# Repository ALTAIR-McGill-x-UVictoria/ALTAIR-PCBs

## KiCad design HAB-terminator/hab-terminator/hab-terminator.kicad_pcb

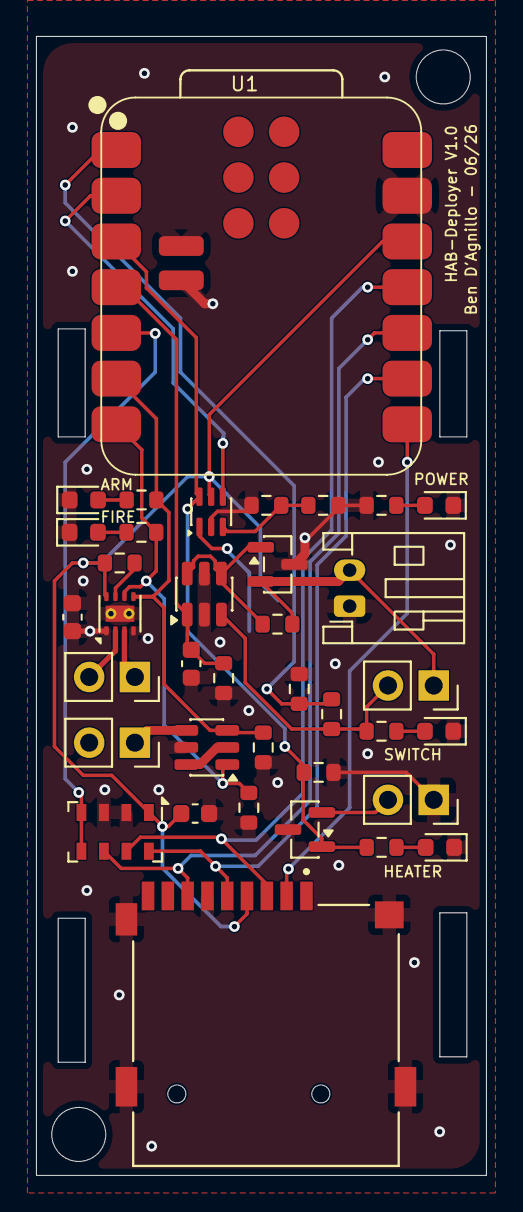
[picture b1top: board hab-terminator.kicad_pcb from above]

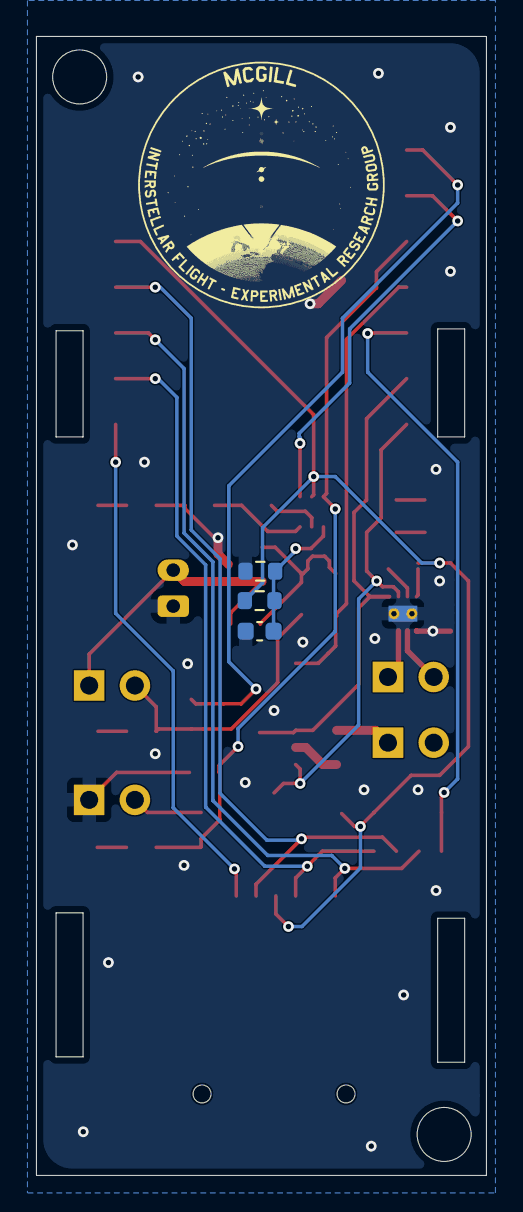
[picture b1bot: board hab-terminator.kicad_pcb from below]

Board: 4 copper layers, 25.0 x 63.3 mm, 40 parts (3 on the bottom side), 29 nets.

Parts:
C2, C4, C6, C7: 100nF; C_0603_1608Metric
D1, D2, D3, D4, D5: LED; LED_0603_1608Metric
J1: Battery; JST_PH_S2B-PH-K_1x02_P2.00mm_Horizontal
J2: Burn wire; PinSocket_1x02_P2.54mm_Vertical
J3: Actuator; PinSocket_1x02_P2.54mm_Vertical
J4: MSD-4-A; CUI_MSD-4-A
J5: Heater; PinSocket_1x02_P2.54mm_Vertical
Q1, Q2: DMN2053UVTQ-7; TSOT-23-6
Q3, Q4: AO3401A; SOT-23
R3, R4, R5, R16, R19: 330; R_0603_1608Metric
R8, R11, R13, R14, R17, R18, R20, R21: 100k; R_0603_1608Metric
R9, R10, R12: 10k; R_0603_1608Metric
SW2: SW_Push_EXT; PinSocket_1x02_P2.54mm_Vertical
TH1: NCU18XH103F60RB; R_0603_1608Metric
U1: XIAO-ESP32-C3-SMD
U2: DRV8212P; WSON-8-1EP_2x2mm_P0.5mm_EP0.9x1.6mm_ThermalVias
U3: 74LVC1G3157; SOT-363_SC-70-6
U4: MS5607-02BA; LGA-8_3x5mm_P1.25mm

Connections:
+3V3: C6.1, J4.4 (VDD), R9.2, R10.2, U1.12 (3V3), U2.8 (VCC), U3.5 (VCC), U4.1 (VDD)
/BURN_ARM/ACT_2: Q1.3 (G), R4.2, R14.1, U1.6 (GPIO7_D5_SCL), U2.5 (IN2)
/BURN_EN/ACT_1: Q1.1 (G), R3.2, R8.1, U1.7 (GPIO21_D6_TX), U2.6 (IN1)
/HEATER_EN/A_MUX: Q4.1 (G), R5.2, R17.2, U1.3 (GPIO4_A2_D2), U3.6
/MS5607_CS: U1.5 (GPIO6_D4_SDA), U4.4 (CSB), U4.5 (CSB)
/NTC: C2.1, R9.1, TH1.1, U3.1
/NTC/VBAT_SNS: U1.2 (GPIO3_A1_D1), U3.4
/PWR_HOLD: C7.2, Q2.1 (G), R12.2, U1.4 (GPIO5_A3_D3)
/SD_CS: J4.2 (CD/DAT3), U1.8 (GPIO20_D7_RX)
/SPI_CLK: J4.5 (CLK), U1.9 (GPIO8_D8_SCK), U4.8 (SCLK)
/SPI_MISO: J4.7 (DAT0), U1.10 (GPIO9_D9_MISO), U4.6 (SDO)
/SPI_MOSI: J4.3 (CMD), U1.11 (GPIO10_D10_MOSI), U4.7 (SDI/SDA)
/SW_SNS: R11.1, R18.2, U1.1 (GPIO2_A0_D0)
/VBAT: J1.2, Q3.2 (S), R13.1, SW2.1
GND: C2.2, C4.1, C4.2, C6.2, C7.1, D1.1 (K), D2.1 (K), D3.1 (K), D4.1 (K), D5.1 (K), J1.1, J4.6 (VSS), J4.G1 (COVER_GND), J4.G2 (COVER_GND__1), J4.G3 (COVER_GND__2), J4.G4 (COVER_GND__3), J5.1, Q1.5 (S), Q2.2 (S), Q2.5 (S), Q3.3 (D), Q4.3 (D), R8.2, R12.1, R14.2, R17.1, R18.1, R19.2, R20.1, R21.1, TH1.2, U1.13 (GND), U1.21 (BAT), U1.22 (GND), U2.1 (VM), U2.4 (GND), U2.9 (GND), U3.2 (GND), U4.2 (PS), U4.3 (GND)
unnamed: D1.2 (A), R3.1
unnamed: D2.2 (A), R4.1
unnamed: D3.2 (A), R16.1
unnamed: D4.2 (A), R19.1
unnamed: D5.2 (A), R5.1
unnamed: J2.1, Q1.4 (D)
unnamed: J3.1, U2.3 (OUT2)
unnamed: J3.2, U2.2 (OUT1)
unnamed: J5.2, Q4.2 (S)
unnamed: Q1.2 (S), Q1.6 (D)
unnamed: Q2.4 (D), Q2.6 (D), Q3.1 (G), R13.2
unnamed: Q2.3 (G), R11.2, R16.2, SW2.2
unnamed: R20.2, R21.2, U3.3
unnamed: R10.1, U2.7 (~SLEEP)

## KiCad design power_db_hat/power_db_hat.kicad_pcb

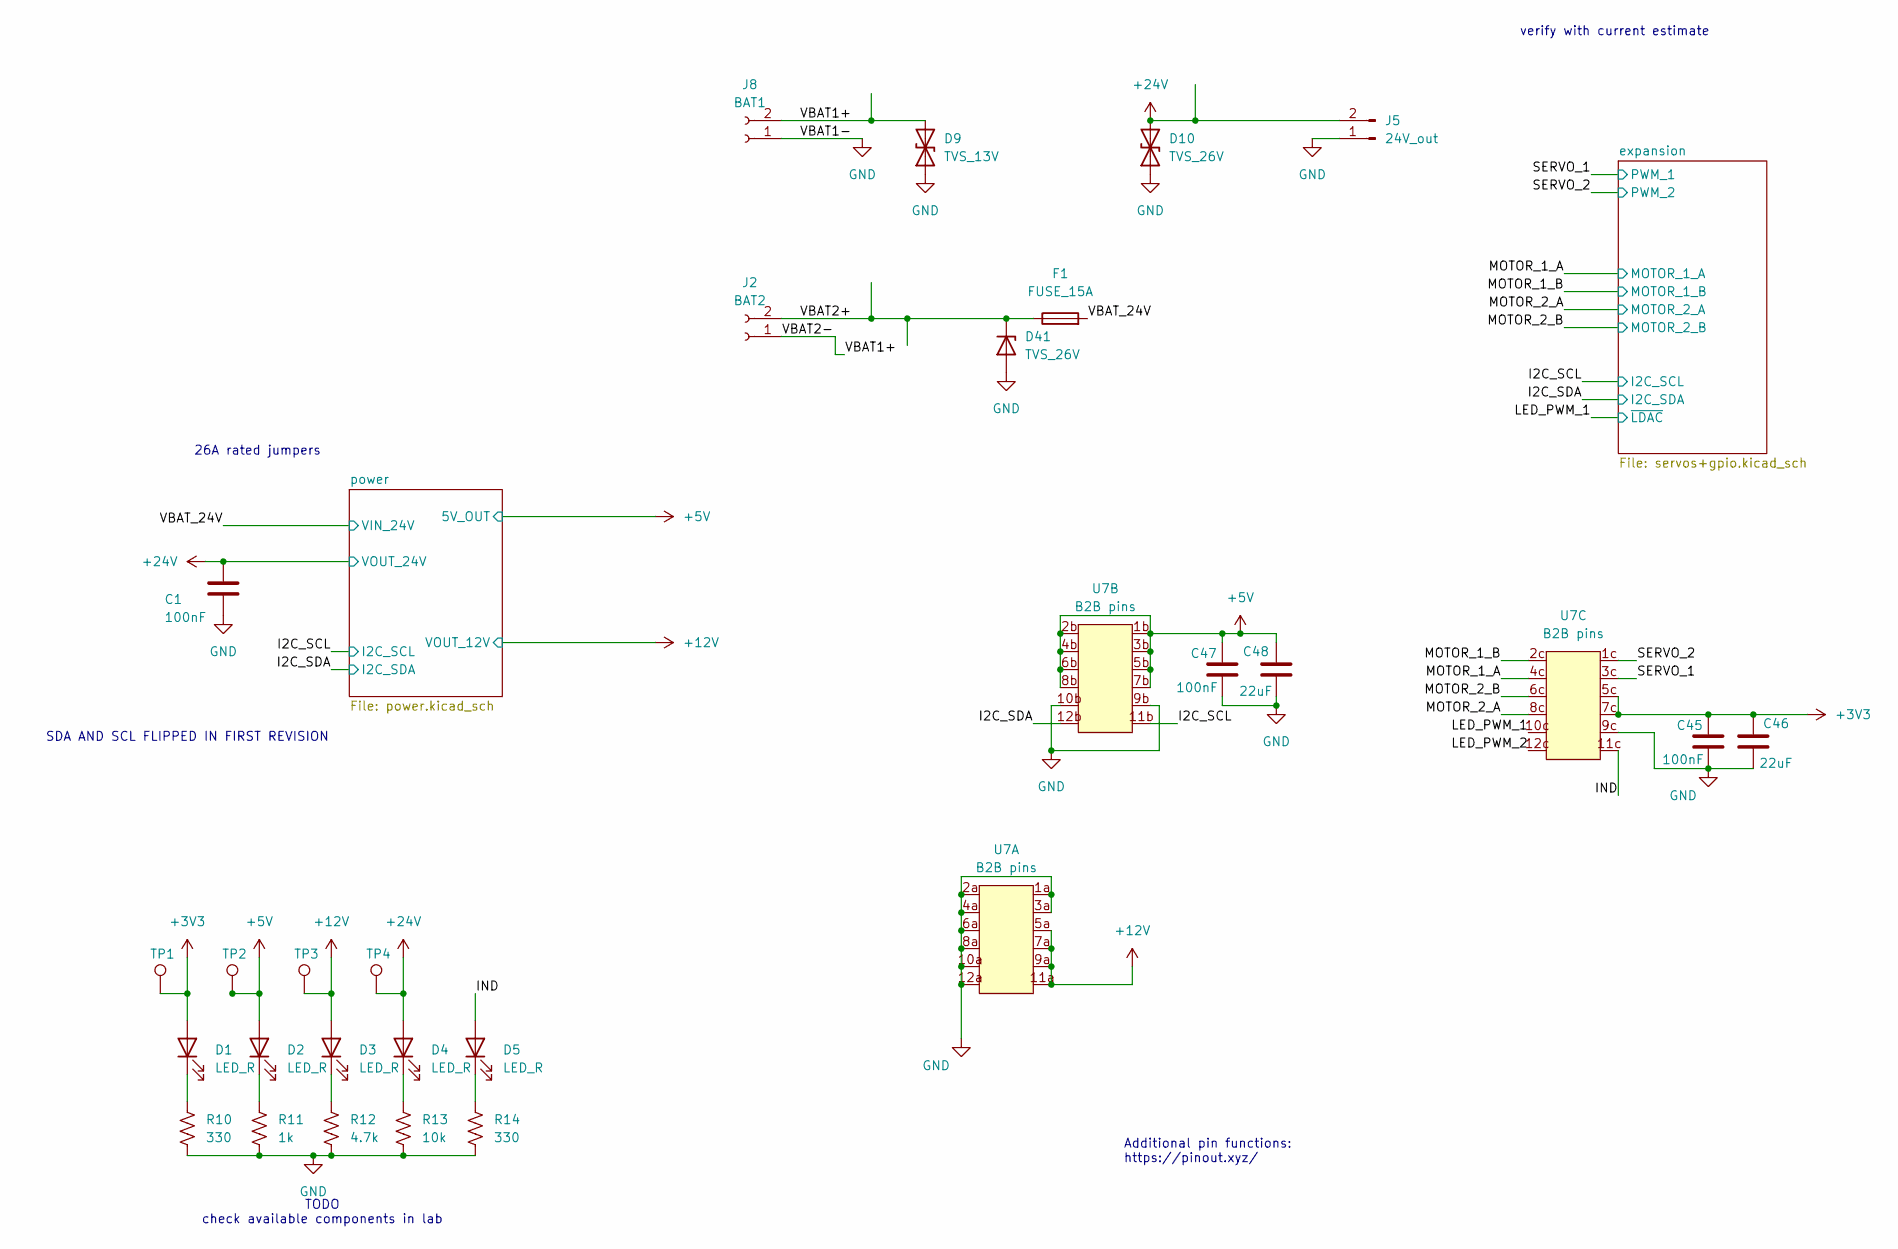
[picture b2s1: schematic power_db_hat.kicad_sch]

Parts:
C1, C45, C47: 100nF; C_0603_1608Metric_Pad1.08x0.95mm_HandSolder
C46, C48: 22uF; C_0805_2012Metric
D1, D2, D3, D4, D5: LED_R; LED_0603_1608Metric_Pad1.05x0.95mm_HandSolder
D9: TVS_13V; D_SMA_Handsoldering
D10, D41: TVS_26V; D_SMA_Handsoldering
F1: FUSE_15A; Fuse_1206_3216Metric_Pad1.42x1.75mm_HandSolder
J2: BAT2; AMASS_XT60PW-M_1x02_P7.20mm_Horizontal
J5: 24V_out; AMASS_XT60PW-F_1x02_P7.20mm_Horizontal
J8: BAT1; AMASS_XT60PW-M_1x02_P7.20mm_Horizontal
R10, R14: 330; R_0603_1608Metric_Pad0.98x0.95mm_HandSolder
R11: 1k; R_0603_1608Metric_Pad0.98x0.95mm_HandSolder
R12: 4.7k; R_0603_1608Metric_Pad0.98x0.95mm_HandSolder
R13: 10k; R_0603_1608Metric_Pad0.98x0.95mm_HandSolder
TP1, TP2, TP3, TP4: TestPoint; TestPoint_Pad_D1.0mm
U7: B2B pins; B2B_pin_socket_3x(02x06)

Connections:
+3V3: C45.2, C46.1, D1.2 (A), TP1.1 (1_1), U7.5c, U7.7c; also elsewhere on the board
+5V: C47.2, C48.1, D2.2 (A), TP2.1 (1_1), U7.1b, U7.2b, U7.3b, U7.4b, U7.5b, U7.6b, U7.7b, U7.8b; also elsewhere on the board
+12V: D3.2 (A), TP3.1 (1_1), U7.5a, U7.7a, U7.9a, U7.11a; also elsewhere on the board
+24V: C1.2, D4.2 (A), D10.2 (A2), J5.2, TP4.1 (1_1); also elsewhere on the board
/I2C_SCL: U7.11b; also elsewhere on the board
/I2C_SDA: U7.12b; also elsewhere on the board
/IND: D5.2 (A), U7.11c
/LED_PWM_1: U7.10c; also elsewhere on the board
/LED_PWM_2: U7.12c
/MOTOR_1_A: U7.4c; also elsewhere on the board
/MOTOR_1_B: U7.2c; also elsewhere on the board
/MOTOR_2_A: U7.8c; also elsewhere on the board
/MOTOR_2_B: U7.6c; also elsewhere on the board
/SERVO_1: U7.3c; also elsewhere on the board
/SERVO_2: U7.1c; also elsewhere on the board
/VBAT1+: D9.2 (A2), J2.1, J8.2
/VBAT2+: D41.1 (K), F1.1, J2.2
/VBAT_24V: F1.2; also elsewhere on the board
GND: C1.1, C45.1, C46.2, C47.1, C48.2, D9.1 (A1), D10.1 (A1), D41.2 (A), J5.1, J8.1, R10.2, R11.2, R12.2, R13.2, R14.2, U7.1a, U7.2a, U7.3a, U7.4a, U7.6a, U7.8a, U7.9b, U7.9c, U7.10a, U7.10b, U7.12a; also elsewhere on the board
unnamed: D1.1 (K), R10.1
unnamed: D2.1 (K), R11.1
unnamed: D3.1 (K), R12.1
unnamed: D4.1 (K), R13.1
unnamed: D5.1 (K), R14.1

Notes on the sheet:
SDA AND SCL FLIPPED IN FIRST REVISION
TODO check available components in lab
Additional pin functions: https://pinout.xyz/
verify with current estimate
26A rated jumpers

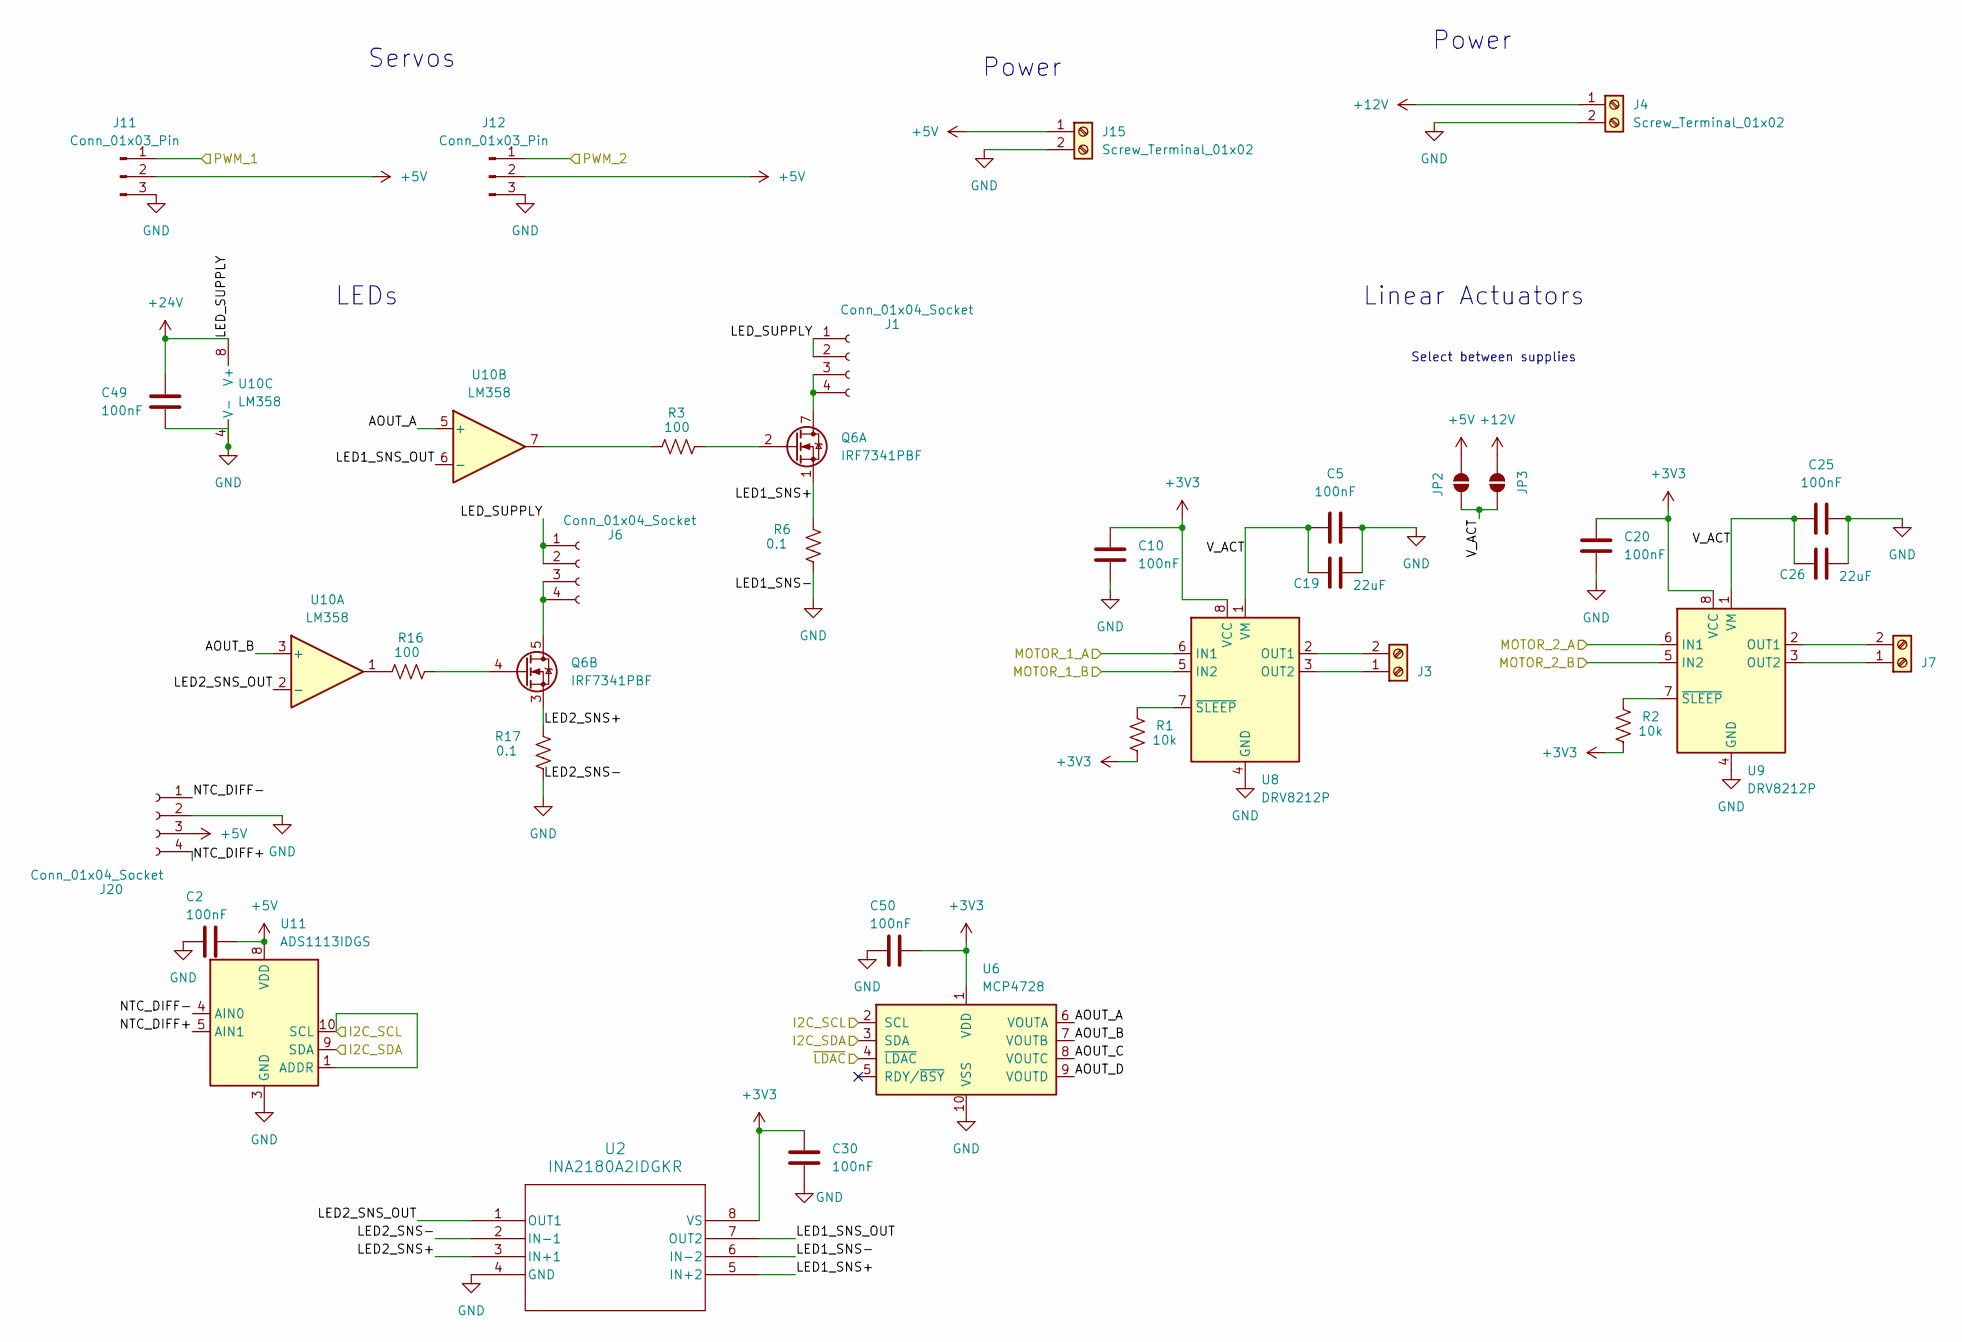
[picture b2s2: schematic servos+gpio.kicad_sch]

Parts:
C2, C5, C10, C20, C25, C30, C49, C50: 100nF; C_0603_1608Metric_Pad1.08x0.95mm_HandSolder
C19, C26: 22uF; C_0805_2012Metric
J1, J6, J20: Conn_01x04_Socket; JST_GH_SM04B-GHS-TB_1x04-1MP_P1.25mm_Horizontal
J3, J4, J7, J15: Screw_Terminal_01x02; 1x02_P2.54mm_Horizontal
J11, J12: Conn_01x03_Pin; FanPinHeader_1x03_P2.54mm_Vertical
JP2, JP3: SolderJumper_2_Open; SolderJumper-2_P1.3mm_Open_TrianglePad1.0x1.5mm
Q6: IRF7341PBF; SOIC-8_3.9x4.9mm_P1.27mm
R1, R2: 10k; R_0603_1608Metric_Pad0.98x0.95mm_HandSolder
R3, R16: 100; R_0603_1608Metric_Pad0.98x0.95mm_HandSolder
R6, R17: 0.1; R_2512_6332Metric
U2: INA2180A2IDGKR; DGK8_TEX
U6: MCP4728; MSOP-10_3x3mm_P0.5mm
U8, U9: DRV8212P; WSON-8-1EP_2x2mm_P0.5mm_EP0.9x1.6mm
U10: LM358; SOIC-8_3.9x4.9mm_P1.27mm
U11: ADS1113IDGS; TSSOP-10_3x3mm_P0.5mm

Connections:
+3V3: C10.1, C20.1, C30.1, C50.1, R1.2, R2.2, U2.8 (VS), U6.1 (VDD), U8.8 (VCC), U9.8 (VCC); also elsewhere on the board
+5V: C2.1, J11.2, J12.2, J15.1, J20.3, JP2.1 (A), U11.8 (VDD); also elsewhere on the board
+12V: J4.1, JP3.1 (A); also elsewhere on the board
+24V: C49.2, J1.1, J1.2, J6.1, J6.2, U10.8 (V+); also elsewhere on the board
/I2C_SCL: U6.2 (SCL), U11.1 (ADDR), U11.10 (SCL); also elsewhere on the board
/I2C_SDA: U6.3 (SDA), U11.9 (SDA); also elsewhere on the board
/LED_PWM_1: U6.4 (~LDAC); also elsewhere on the board
/MOTOR_1_A: U8.6 (IN1); also elsewhere on the board
/MOTOR_1_B: U8.5 (IN2); also elsewhere on the board
/MOTOR_2_A: U9.6 (IN1); also elsewhere on the board
/MOTOR_2_B: U9.5 (IN2); also elsewhere on the board
/SERVO_1: J11.1; also elsewhere on the board
/SERVO_2: J12.1; also elsewhere on the board
/expansion/AOUT_A: U6.6 (VOUTA), U10.5 (+)
/expansion/AOUT_B: U6.7 (VOUTB), U10.3 (+)
/expansion/AOUT_C: U6.8 (VOUTC)
/expansion/AOUT_D: U6.9 (VOUTD)
/expansion/LED1_SNS+: Q6.1 (S1), R6.2, U2.5 (IN+2)
/expansion/LED1_SNS_OUT: U2.7 (OUT2), U10.6 (-)
/expansion/LED2_SNS+: Q6.3 (S2), R17.2, U2.3 (IN+1)
/expansion/LED2_SNS_OUT: U2.1 (OUT1), U10.2 (-)
/expansion/NTC_DIFF+: J20.4, U11.5 (AIN1)
/expansion/NTC_DIFF-: J20.1, U11.4 (AIN0)
/expansion/V_ACT: C5.1, C19.1, C25.1, C26.1, JP2.2 (B), JP3.2 (B), U8.1 (VM), U9.1 (VM)
GND: C2.2, C5.2, C10.2, C19.2, C20.2, C25.2, C26.2, C30.2, C49.1, C50.2, J4.2, J11.3, J12.3, J15.2, J20.2, R6.1, R17.1, U2.2 (IN-1), U2.4 (GND), U2.6 (IN-2), U6.10 (VSS), U8.4 (GND), U8.9 (GND), U9.4 (GND), U9.9 (GND), U10.4 (V-), U11.3 (GND); also elsewhere on the board
unnamed: J1.3, J1.4, Q6.7 (D1), Q6.8 (D1)
unnamed: J3.1, U8.3 (OUT2)
unnamed: J3.2, U8.2 (OUT1)
unnamed: J6.3, J6.4, Q6.5 (D2), Q6.6 (D2)
unnamed: J7.1, U9.3 (OUT2)
unnamed: J7.2, U9.2 (OUT1)
unnamed: Q6.2 (G1), R3.2
unnamed: Q6.4 (G2), R16.2
unnamed: R3.1, U10.7
unnamed: R16.1, U10.1
unnamed: R1.1, U8.7 (~SLEEP)
unnamed: R2.1, U9.7 (~SLEEP)

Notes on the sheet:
Select between supplies
LEDs
Servos
Linear Actuators
Power

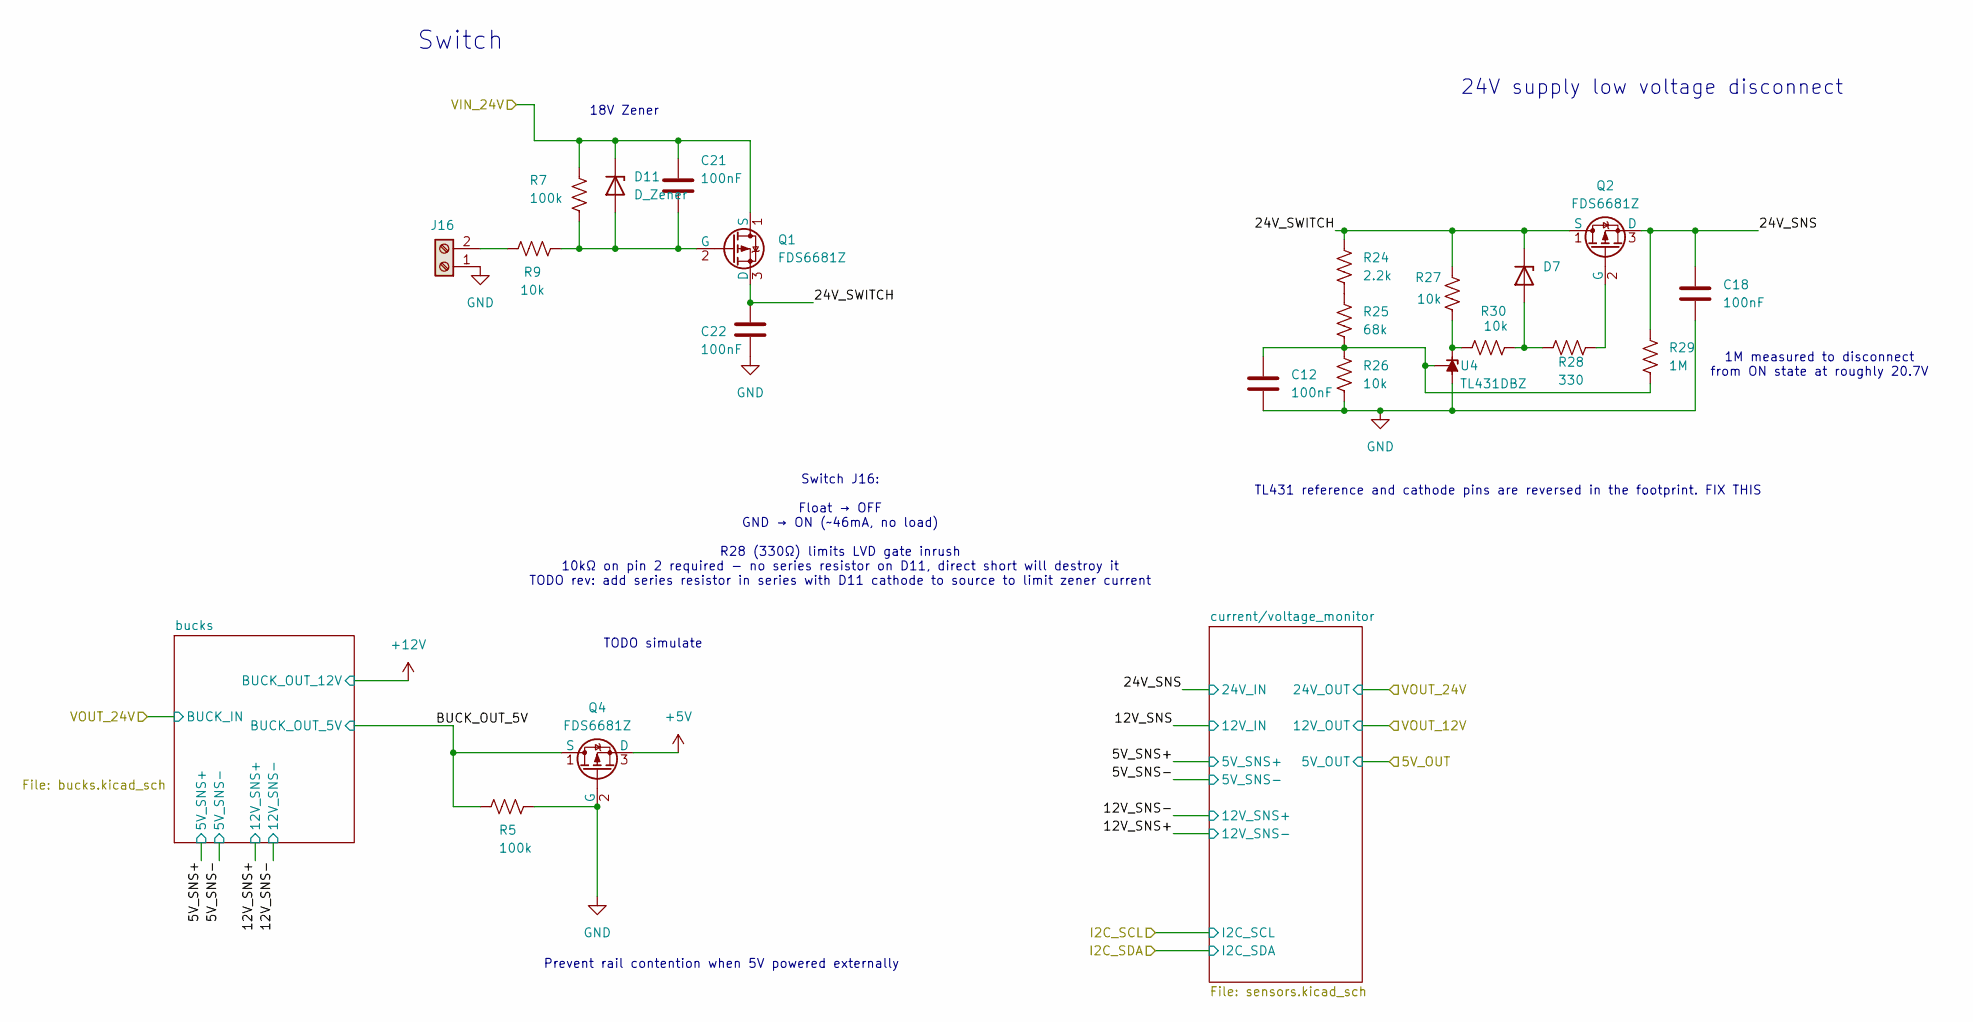
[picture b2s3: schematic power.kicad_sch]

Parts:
C12, C18, C21, C22: 100nF; C_0603_1608Metric_Pad1.08x0.95mm_HandSolder
D7, D11: D_Zener; D_SOD-323_HandSoldering
J16: Screw_Terminal_01x02; 1x02_P2.54mm_Horizontal
Q1, Q2, Q4: FDS6681Z; FDS6681Z_SOP-8
R5, R7: 100k; R_0603_1608Metric_Pad0.98x0.95mm_HandSolder
R9, R26, R27, R30: 10k; R_0603_1608Metric_Pad0.98x0.95mm_HandSolder
R24: 2.2k; R_0603_1608Metric_Pad0.98x0.95mm_HandSolder
R25: 68k; R_0603_1608Metric_Pad0.98x0.95mm_HandSolder
R28: 330; R_0603_1608Metric_Pad0.98x0.95mm_HandSolder
R29: 1M; R_0603_1608Metric_Pad0.98x0.95mm_HandSolder
U4: TL431DBZ; DBZ0003A_L

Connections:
+5V: Q4.3 (D); also elsewhere on the board
/VBAT_24V: C21.1, D11.1 (K), Q1.1 (S), R7.1; also elsewhere on the board
/power/5V_SNS-: Q4.1 (S), R5.2; also elsewhere on the board
/power/24V_SNS: C18.1, Q2.3 (D), R29.1; also elsewhere on the board
/power/24V_SWITCH: C22.1, D7.1 (K), Q1.3 (D), Q2.1 (S), R24.1, R27.1
GND: C12.2, C18.2, C22.2, J16.1, Q4.2 (G), R5.1, R26.2, U4.3 (A); also elsewhere on the board
unnamed: D7.2 (A), R28.1, R30.1
unnamed: C21.2, D11.2 (A), Q1.2 (G), R7.2, R9.2
unnamed: J16.2, R9.1
unnamed: Q2.2 (G), R28.2
unnamed: R24.2, R25.1
unnamed: R27.2, R30.2, U4.1 (K)
unnamed: C12.1, R25.2, R26.1, R29.2, U4.2 (REF)

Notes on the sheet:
TODO simulate
Switch J16: Float → OFF GND → ON (~46mA, no load) R28 (330Ω) limits LVD gate inrush 10kΩ on pin 2 required - no series resistor on D11, direct short will destroy it TODO rev: add series resistor in series with D11 cathode to source to limit zener current
TL431 reference and cathode pins are reversed in the footprint. FIX THIS
24V supply low voltage disconnect
Switch
18V Zener
1M measured to disconnect from ON state at roughly 20.7V
Prevent rail contention when 5V powered externally

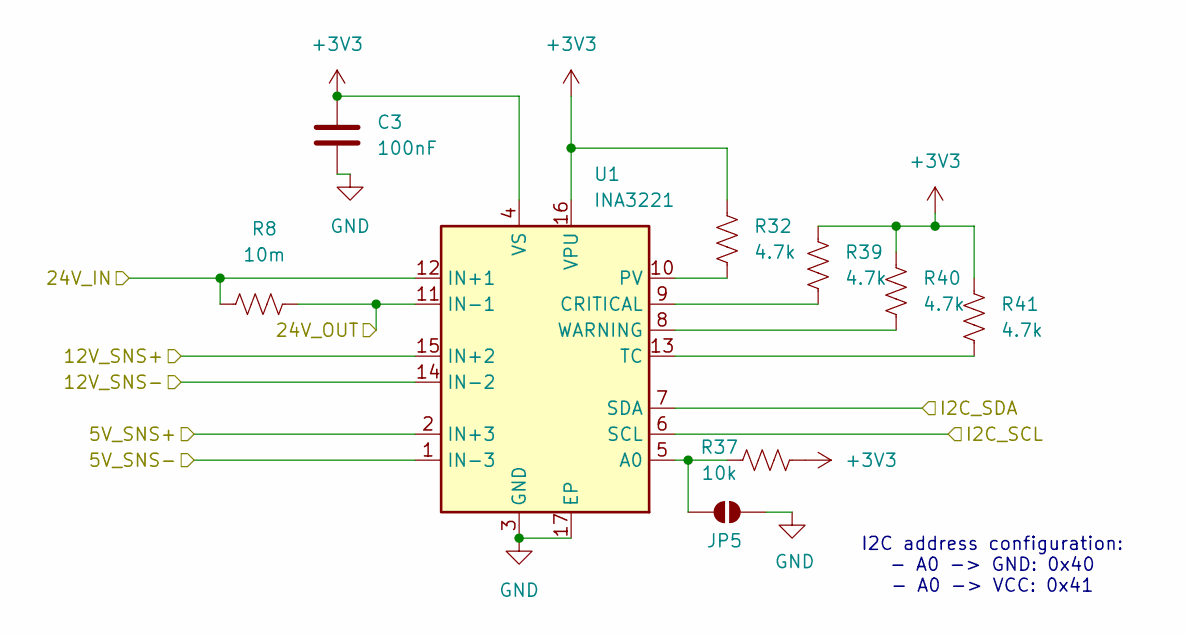
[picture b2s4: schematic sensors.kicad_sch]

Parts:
C3: 100nF; C_0603_1608Metric_Pad1.08x0.95mm_HandSolder
JP5: SolderJumper_2_Open; SolderJumper-2_P1.3mm_Open_TrianglePad1.0x1.5mm
R8: 10m; R_2512_6332Metric_Pad1.40x3.35mm_HandSolder
R32, R39, R40, R41: 4.7k; R_0603_1608Metric_Pad0.98x0.95mm_HandSolder
R37: 10k; R_0603_1608Metric_Pad0.98x0.95mm_HandSolder
U1: INA3221; QFN65P400X400X100-17N-D

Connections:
+3V3: C3.1, R32.1, R37.1, R39.1, R40.1, R41.1, U1.4 (VS), U1.16 (VPU); also elsewhere on the board
+12V: U1.15 (IN+2); also elsewhere on the board
+24V: R8.1, U1.11 (IN-1); also elsewhere on the board
/I2C_SCL: U1.6 (SCL); also elsewhere on the board
/I2C_SDA: U1.7 (SDA); also elsewhere on the board
/power/5V_SNS+: U1.2 (IN+3); also elsewhere on the board
/power/5V_SNS-: U1.1 (IN-3); also elsewhere on the board
/power/12V_SNS+: U1.14 (IN-2); also elsewhere on the board
/power/24V_SNS: R8.2, U1.12 (IN+1); also elsewhere on the board
GND: C3.2, JP5.2 (B), U1.3 (GND), U1.17 (EP); also elsewhere on the board
unnamed: JP5.1 (A), R37.2, U1.5 (A0)
unnamed: R39.2, U1.9 (CRITICAL)
unnamed: R32.2, U1.10 (PV)
unnamed: R41.2, U1.13 (TC)
unnamed: R40.2, U1.8 (WARNING)

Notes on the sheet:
I2C address configuration: - A0 -> GND: 0x40 - A0 -> VCC: 0x41

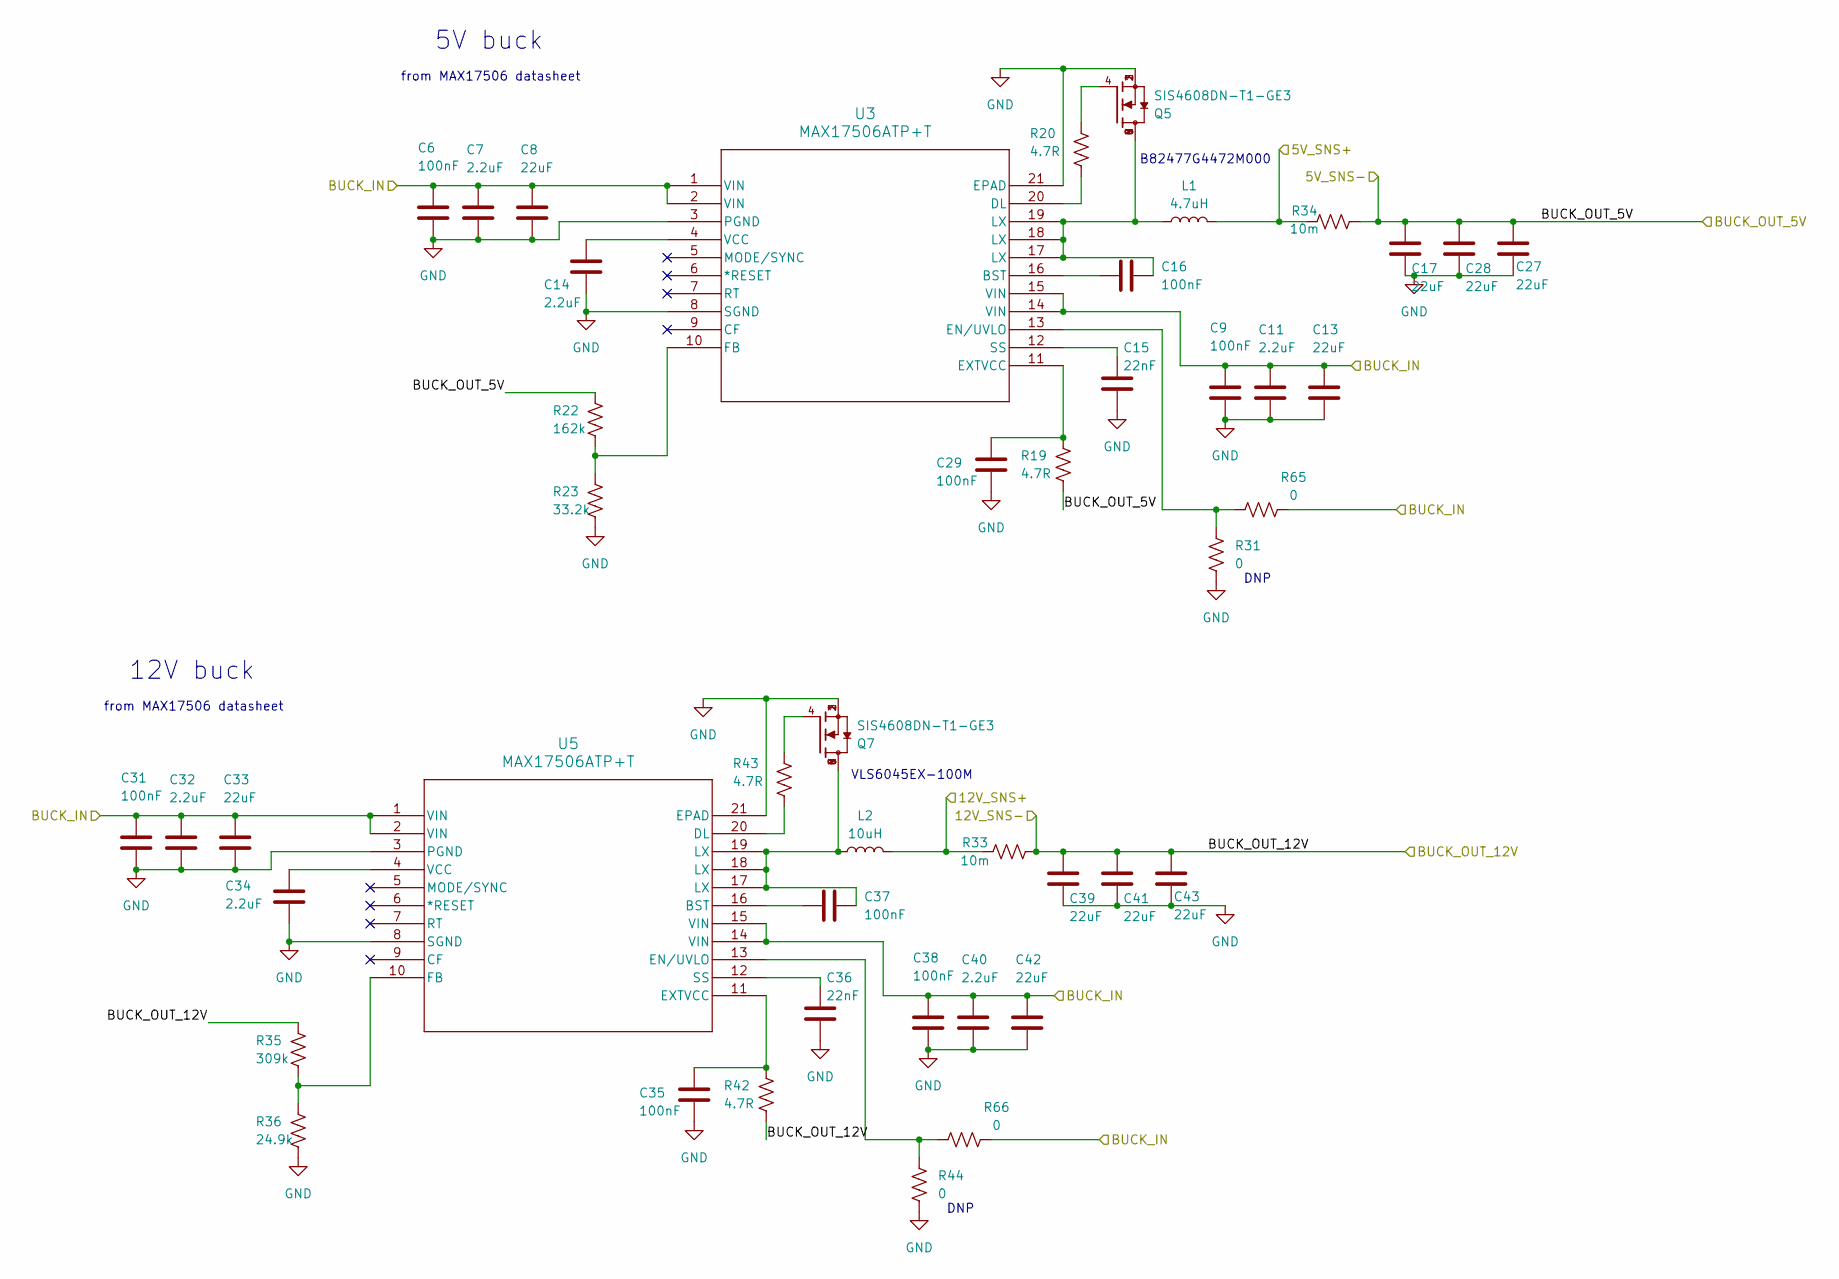
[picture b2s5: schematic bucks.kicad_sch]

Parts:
C6, C9, C16, C29, C31, C35, C37, C38: 100nF; C_0603_1608Metric_Pad1.08x0.95mm_HandSolder
C7, C11, C14, C32, C34, C40: 2.2uF; C_0603_1608Metric_Pad1.08x0.95mm_HandSolder
C8, C13, C17, C27, C28, C33, C39, C42, C43: 22uF; C_0805_2012Metric
C15, C36: 22nF; C_0603_1608Metric_Pad1.08x0.95mm_HandSolder
C41: 22uF; C_0603_1608Metric_Pad1.08x0.95mm_HandSolder
L1: 4.7uH; IND_B82477G4472M000
L2: 10uH; L_TDK_VLS6045EX_VLS6045AF
Q5, Q7: SIS4608DN-T1-GE3; Vishay_PowerPAK_1212-8_Single; PARTREV A
R19, R20, R42, R43: 4.7R; R_0603_1608Metric_Pad0.98x0.95mm_HandSolder
R22: 162k; R_0603_1608Metric_Pad0.98x0.95mm_HandSolder
R23: 33.2k; R_0603_1608Metric_Pad0.98x0.95mm_HandSolder
R31, R44, R65, R66: 0; R_0603_1608Metric_Pad0.98x0.95mm_HandSolder
R33, R34: 10m; R_2512_6332Metric_Pad1.40x3.35mm_HandSolder
R35: 309k; R_0603_1608Metric_Pad0.98x0.95mm_HandSolder
R36: 24.9k; R_0603_1608Metric_Pad0.98x0.95mm_HandSolder
U3, U5: MAX17506ATP+T; 21-0140L_T2055-4_MXM

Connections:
+12V: C39.1, C41.1, C43.1, R33.1, R35.1, R42.2; also elsewhere on the board
+24V: C6.1, C7.1, C8.1, C9.1, C11.1, C13.1, C31.1, C32.1, C33.1, C38.1, C40.1, C42.1, R65.1, R66.1, U3.1 (VIN), U3.2 (VIN), U3.14 (VIN), U3.15 (VIN), U5.1 (VIN), U5.2 (VIN), U5.14 (VIN), U5.15 (VIN); also elsewhere on the board
/power/5V_SNS+: L1.2, R34.2; also elsewhere on the board
/power/5V_SNS-: C17.1, C27.1, C28.1, R19.2, R22.1, R34.1; also elsewhere on the board
/power/12V_SNS+: L2.2, R33.2; also elsewhere on the board
GND: C6.2, C7.2, C8.2, C9.2, C11.2, C13.2, C14.2, C15.2, C17.2, C27.2, C28.2, C29.2, C31.2, C32.2, C33.2, C34.2, C35.2, C36.2, C38.2, C39.2, C40.2, C41.2, C42.2, C43.2, Q5.1, Q5.2, Q5.3, Q7.1, Q7.2, Q7.3, R23.2, R31.2, R36.2, R44.2, U3.3 (PGND), U3.8 (SGND), U3.21 (EPAD), U5.3 (PGND), U5.8 (SGND), U5.21 (EPAD); also elsewhere on the board
unnamed: C16.2, L1.1, Q5.5, Q5.6, Q5.7, Q5.8, Q5.9, U3.17 (LX), U3.18 (LX), U3.19 (LX)
unnamed: C37.2, L2.1, Q7.5, Q7.6, Q7.7, Q7.8, Q7.9, U5.17 (LX), U5.18 (LX), U5.19 (LX)
unnamed: Q5.4, R20.1
unnamed: Q7.4, R43.1
unnamed: C16.1, U3.16 (BST)
unnamed: R20.2, U3.20 (DL)
unnamed: R31.1, R65.2, U3.13 (EN/UVLO)
unnamed: C29.1, R19.1, U3.11 (EXTVCC)
unnamed: R22.2, R23.1, U3.10 (FB)
unnamed: C15.1, U3.12 (SS)
unnamed: C14.1, U3.4 (VCC)
unnamed: C37.1, U5.16 (BST)
unnamed: R43.2, U5.20 (DL)
unnamed: R44.1, R66.2, U5.13 (EN/UVLO)
unnamed: C35.1, R42.1, U5.11 (EXTVCC)
unnamed: R35.2, R36.1, U5.10 (FB)
unnamed: C36.1, U5.12 (SS)
unnamed: C34.1, U5.4 (VCC)

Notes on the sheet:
5V buck
from MAX17506 datasheet
DNP
12V buck
VLS6045EX-100M
B82477G4472M000

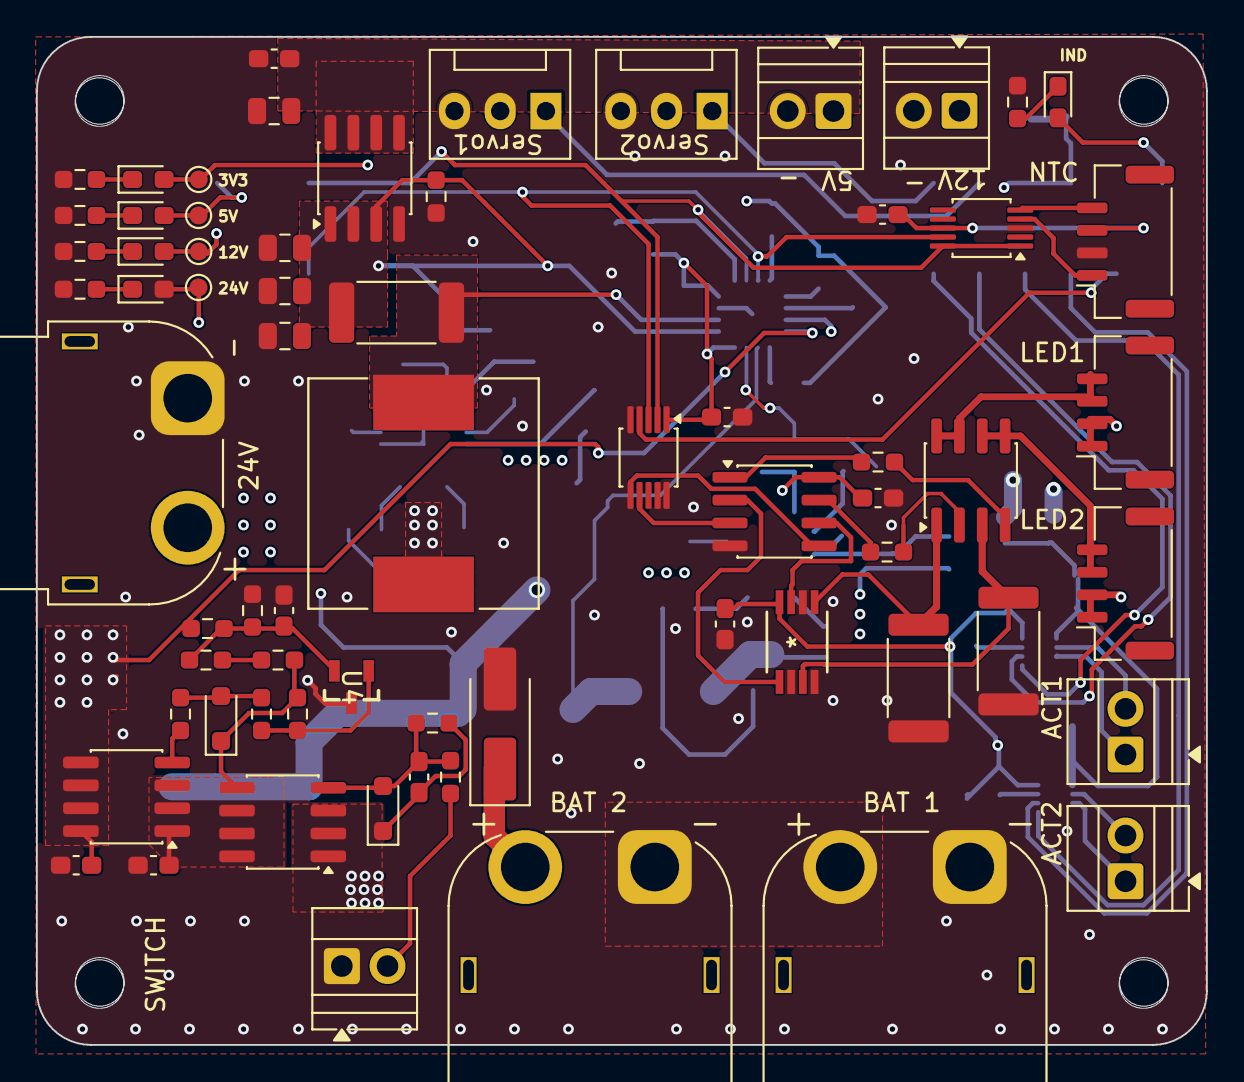
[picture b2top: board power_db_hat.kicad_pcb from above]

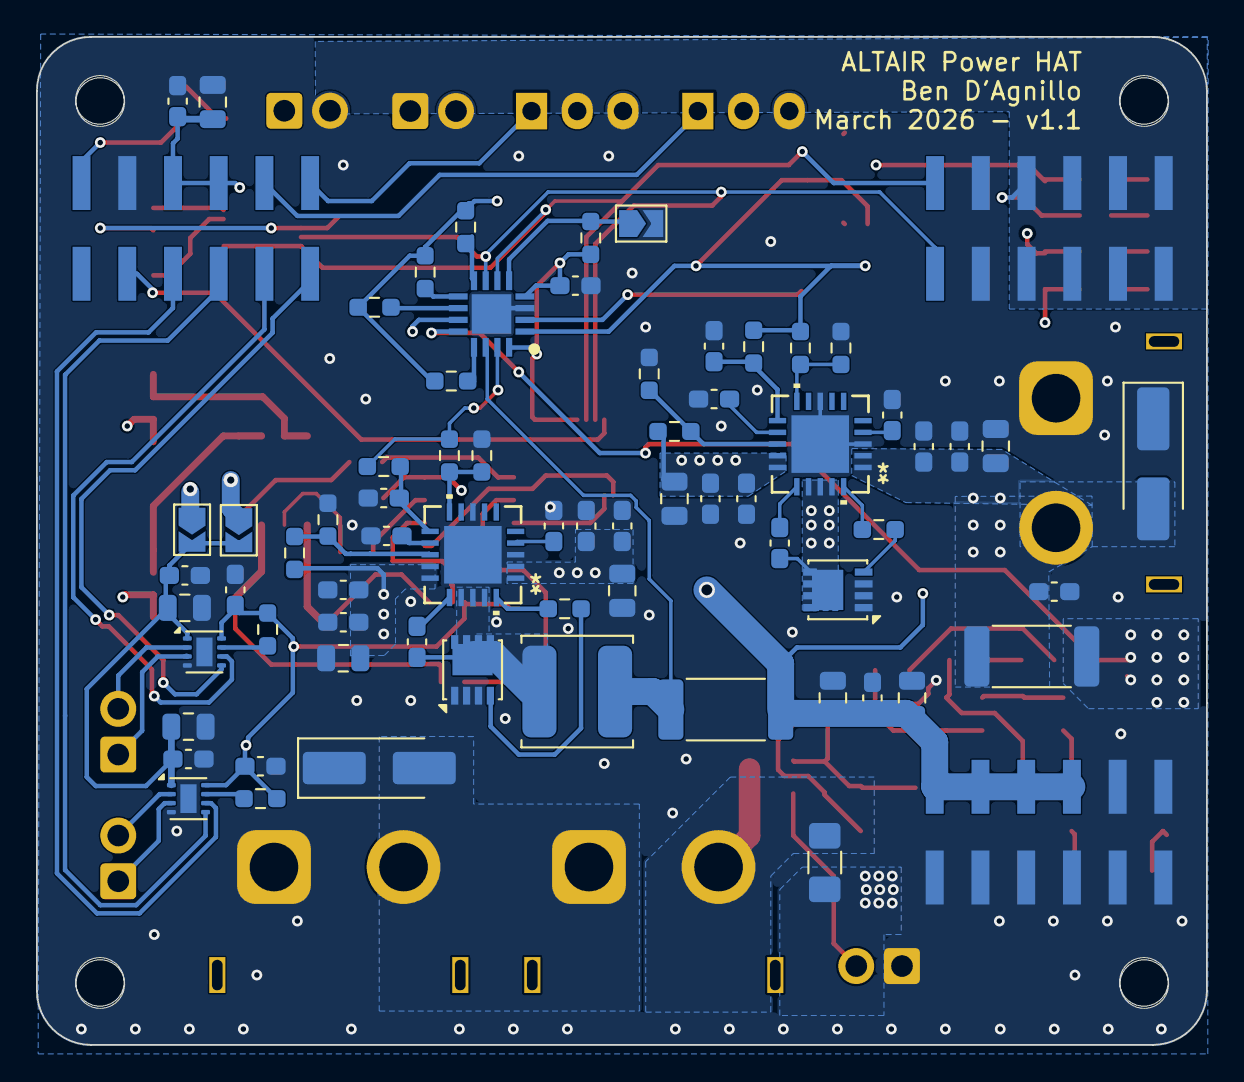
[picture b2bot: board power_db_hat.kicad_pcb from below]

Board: 4 copper layers, 65.0 x 56.0 mm, 141 parts (68 on the bottom side), 79 nets.

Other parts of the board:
MH1, MH2, MH3, MH4: MountingHole_2.7mm_M2.5
